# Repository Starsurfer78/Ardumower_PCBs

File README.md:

DIY Robot Lawn Mower Community: https://www.diy-robot-lawn-mower.com/

# Simple Ardumower_PCBs

If you want to buy a Board, you can send me an E-Mail: info@projekt-heimwerken.de

# Simple MainPCB only for Arduino DUE or Grand Central

New Board Design. All Pins from Software are now on the PCB. 
Supports 4 Motor Driver for Mowing.
Only a few Electronic Parts are needed. 
- JST-XH Connectors
- Screw Terminal 5.04mm
- Resistors
- Pin Header Connector 2.54mm
- Active Buzzer
- LED
- Jumper

Tested with MC33926 motor driver. Brushless Motordriver did not work at the Moment with Azuritber.

# Power PCB for Simple MainPCB

The charging board and the power supply for the motors are on a separate board.

Should also fit into small housings.

Use it at your own Risk.

Projekt: https://forum.ardumower.de/

Software Azuritber: https://github.com/Boilevin/AzuritBer

Ardumower Original Software: https://github.com/Ardumower

Facebook Gruppe DIY Robot Lawn Mower: https://www.facebook.com/groups/319588508137220

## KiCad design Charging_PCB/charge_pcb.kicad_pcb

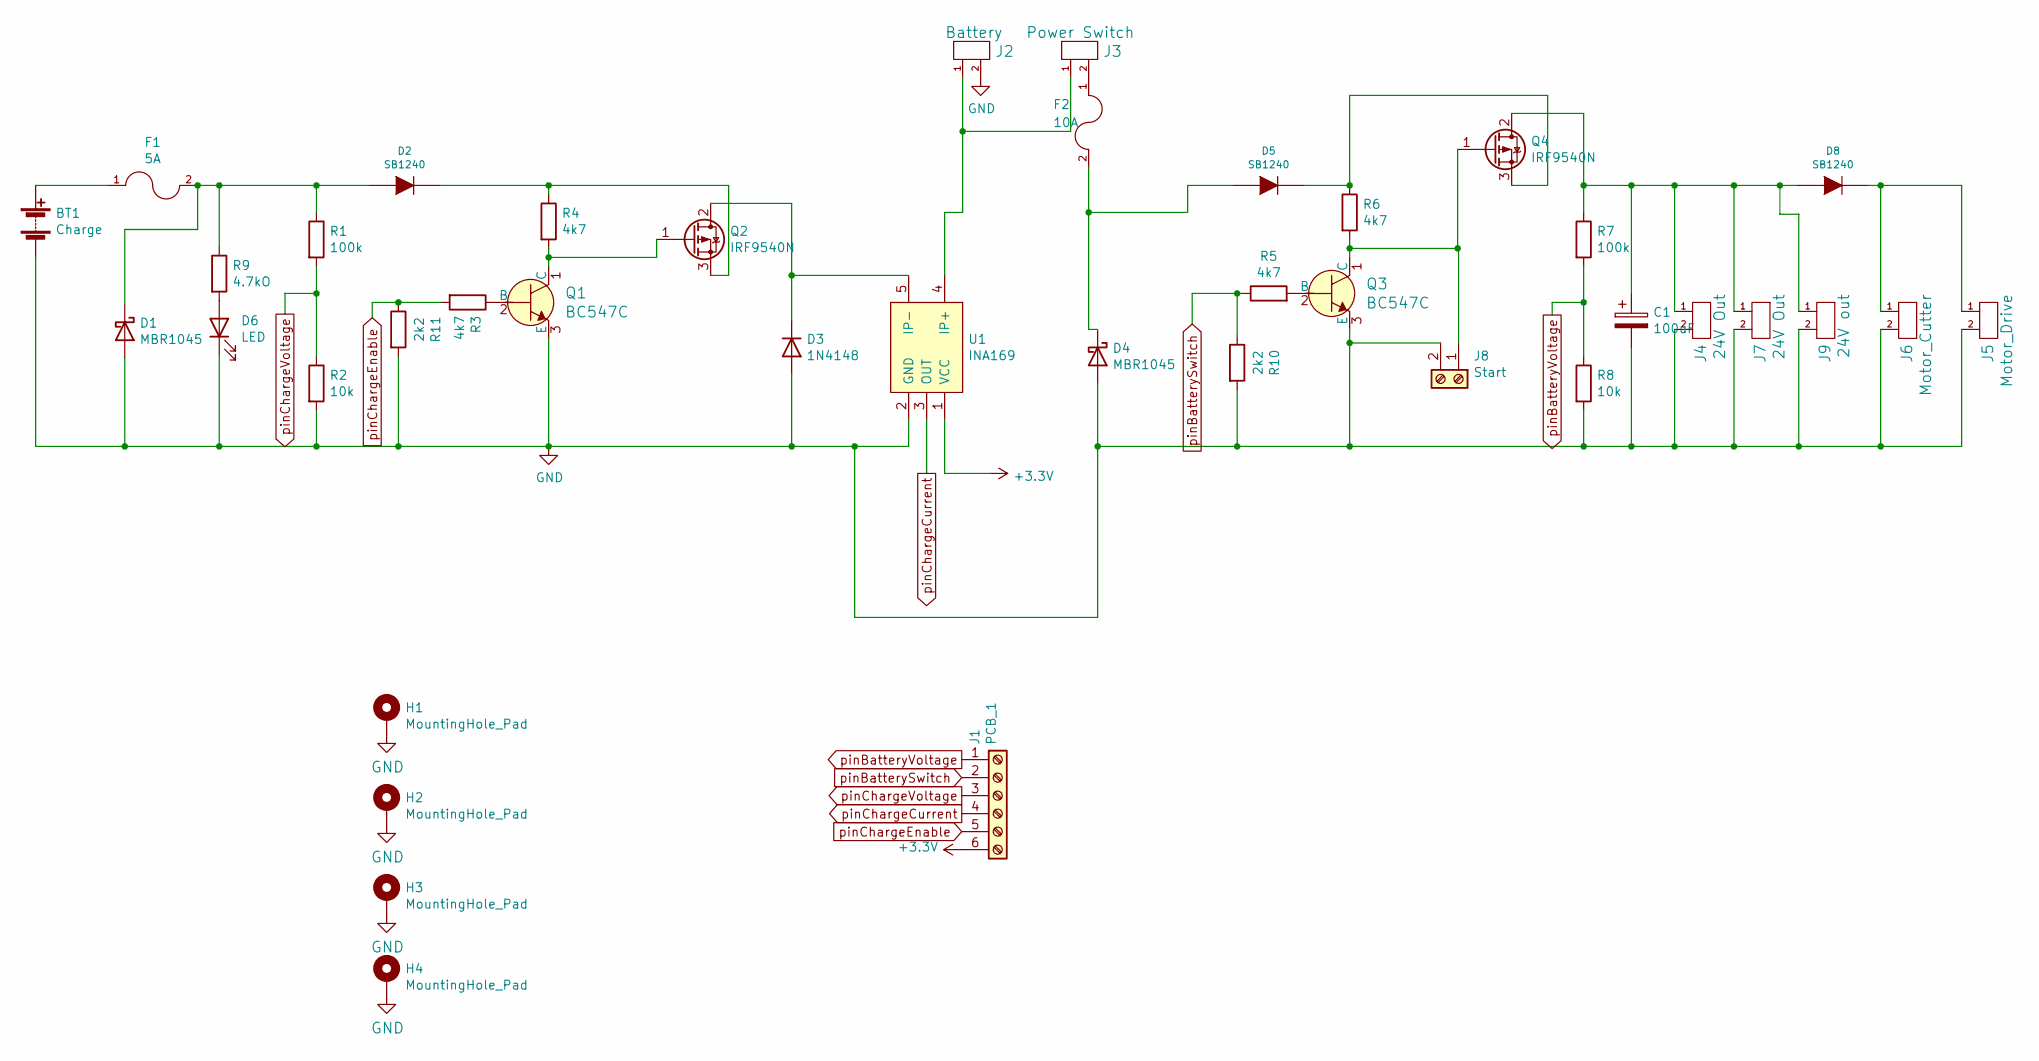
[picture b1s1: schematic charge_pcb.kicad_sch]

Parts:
BT1: Charge; Anschlussklemme_2P_RM5,08
C1: 100uF; Elko_vert_11.2x6.3mm_RM2.5
D1, D4: MBR1045; TO-220-2_Vertical
D2, D5, D8: SB1240; D_DO-41_SOD81_P10.16mm_Horizontal
D3: 1N4148; D_DO-35_SOD27_P7.62mm_Horizontal
D6: LED; LED_D1.8mm_W3.3mm_H2.4mm
F1: 5A; Fuseholder_Reichelt_PL112000
F2: 10A; Fuseholder_Reichelt_PL112000
H1, H2, H3, H4: MountingHole_Pad; MountingHole_3.2mm_M3_DIN965_Pad_TopBottom
J1: PCB_1; JST_XH_B6B-XH-A_1x06_P2.50mm_Vertical
J2: Battery; TerminalBlock_bornier-2_P5.08mm
J3: Power Switch; TerminalBlock_bornier-2_P5.08mm
J4, J7: 24V Out; TerminalBlock_bornier-2_P5.08mm
J5: Motor_Drive; TerminalBlock_bornier-2_P5.08mm
J6: Motor_Cutter; TerminalBlock_bornier-2_P5.08mm
J8: Start; JST_XH_B2B-XH-A_1x02_P2.50mm_Vertical
J9: 24V out; TerminalBlock_bornier-2_P5.08mm
Q1, Q3: BC547C; TO-92-3_Formed_Leads; MPN BC548BTA; Digi-Key_PN BC548BTACT-ND
Q2, Q4: IRF9540N; TO-220-3_Vertical
R1, R7: 100k; R_Axial_DIN0207_L6.3mm_D2.5mm_P7.62mm_Horizontal
R2, R8: 10k; R_Axial_DIN0207_L6.3mm_D2.5mm_P7.62mm_Horizontal
R3, R4, R5, R6: 4k7; R_Axial_DIN0207_L6.3mm_D2.5mm_P7.62mm_Horizontal
R9: 4.7kO; R_Axial_DIN0207_L6.3mm_D2.5mm_P7.62mm_Horizontal
R10, R11: 2k2; R_Axial_DIN0207_L6.3mm_D2.5mm_P7.62mm_Horizontal
U1: INA169; INA169_mit_Pinnummern

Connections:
+3V3: J1.6, U1.1 (VCC)
GND: BT1.2 (-), C1.2, D1.2 (A), D3.2 (A), D4.2 (A), D6.1 (K), H1.1, H2.1, H3.1, H4.1, J2.2, J4.2, J5.2, J6.2, J7.2, J8.2, J9.2, Q1.3 (E), Q3.3 (E), R2.2, R8.2, R10.2, R11.2, U1.2 (GND)
unnamed: BT1.1 (+), F1.1
unnamed: C1.1, D8.1 (A), J4.1, J7.1, J9.1, Q4.2 (D), R7.1
unnamed: D1.1 (K), D2.1 (A), F1.2, R1.1, R9.1
unnamed: D2.2 (K), Q2.3 (S), R4.1
unnamed: D3.1 (K), Q2.2 (D), U1.5 (IP-)
unnamed: D4.1 (K), D5.1 (A), F2.2
unnamed: D5.2 (K), Q4.3 (S), R6.1
unnamed: D6.2 (A), R9.2
unnamed: D8.2 (K), J5.1, J6.1
unnamed: F2.1, J3.2
unnamed: J2.1, J3.1, U1.4 (IP+)
unnamed: J8.1, Q3.1 (C), Q4.1 (G), R6.2
unnamed: Q1.1 (C), Q2.1 (G), R4.2
unnamed: Q1.2 (B), R3.1
unnamed: Q3.2 (B), R5.2
pinBatterySwitch: J1.2, R5.1, R10.1
pinBatteryVoltage: J1.1, R7.2, R8.1
pinChargeCurrent: J1.4, U1.3 (OUT)
pinChargeEnable: J1.5, R3.2, R11.1
pinChargeVoltage: J1.3, R1.2, R2.1

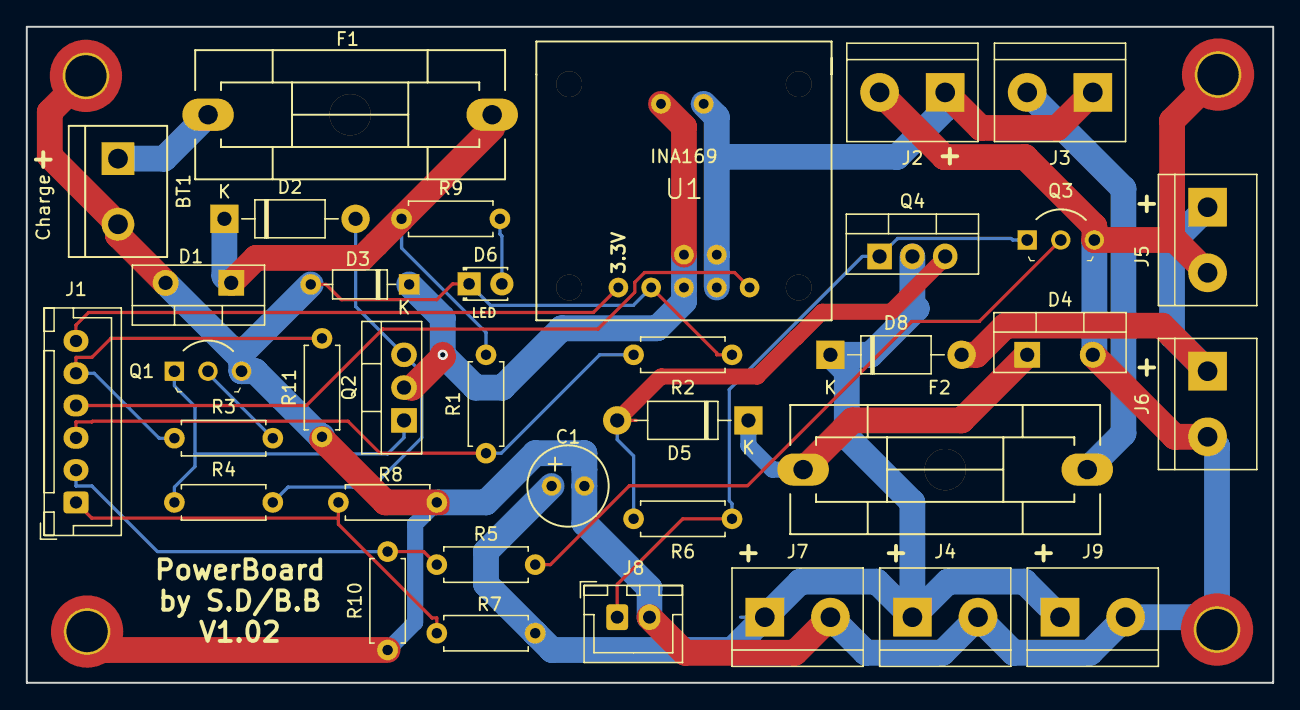
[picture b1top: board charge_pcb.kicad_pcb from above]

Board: 2 copper layers, 96.5 x 50.8 mm, 40 parts (0 on the bottom side), 22 nets.

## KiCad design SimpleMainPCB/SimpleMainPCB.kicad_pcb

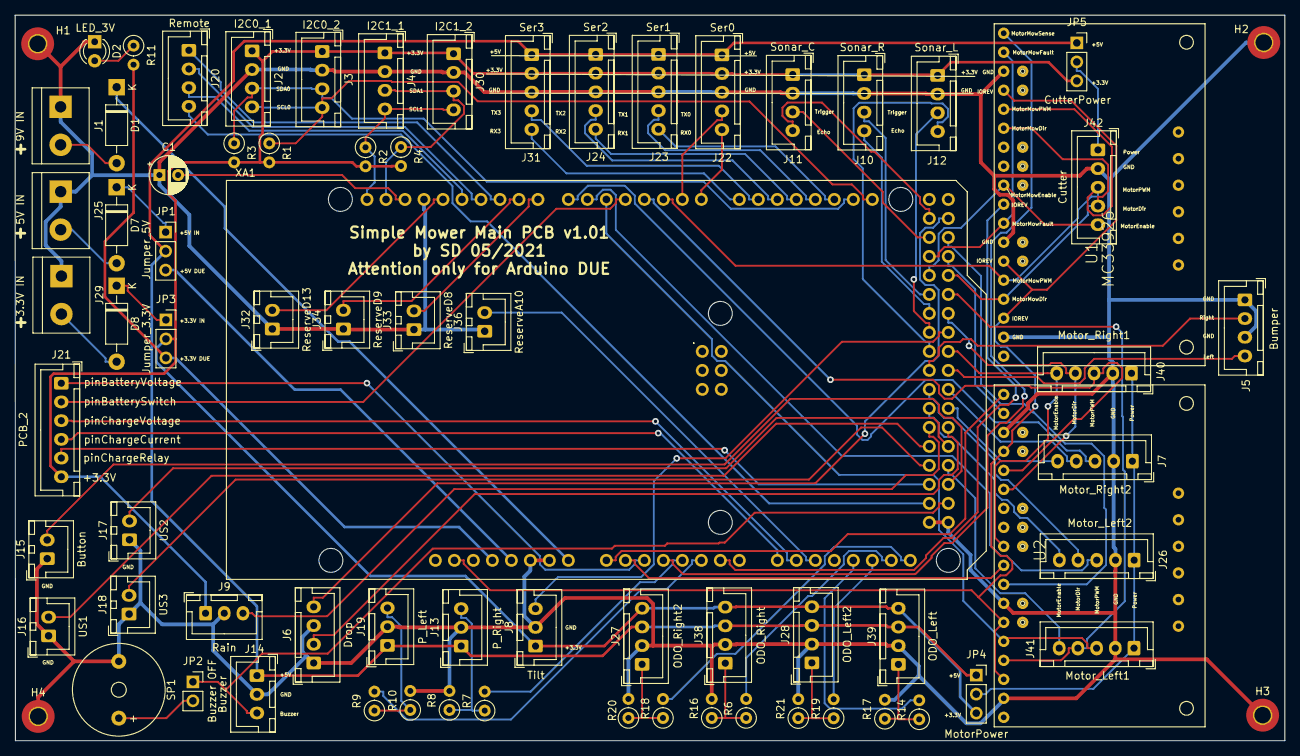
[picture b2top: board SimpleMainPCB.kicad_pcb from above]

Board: 2 copper layers, 169.8 x 97.0 mm, 75 parts (0 on the bottom side), 93 nets.

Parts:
C1: 100nF; CP_Radial_D5.0mm_P2.50mm
D1, D7, D8: 1N5819; D_DO-41_SOD81_P10.16mm_Horizontal
D2: LED_3V; LED_D3.0mm
H1, H2, H3, H4: MountingHole_Pad; MountingHole_2.2mm_M2_Pad_TopBottom
J1: 9V IN; TerminalBlock_bornier-2_P5.08mm
J2: I2C0_1; JST_XH_B4B-XH-A_1x04_P2.50mm_Vertical
J3: I2C0_2; JST_XH_B4B-XH-A_1x04_P2.50mm_Vertical
J4: I2C1_1; JST_XH_B4B-XH-A_1x04_P2.50mm_Vertical
J5: Bumper; JST_XH_B4B-XH-A_1x04_P2.50mm_Vertical
J6: Drop; JST_XH_B4B-XH-A_1x04_P2.50mm_Vertical
J7: Motor_Right2; JST_XH_B5B-XH-A_1x05_P2.50mm_Vertical
J8: Tilt; JST_XH_B3B-XH-A_1x03_P2.50mm_Vertical
J9: Rain; JST_XH_B3B-XH-A_1x03_P2.50mm_Vertical
J10: Sonar_R; JST_XH_B4B-XH-A_1x04_P2.50mm_Vertical
J11: Sonar_C; JST_XH_B4B-XH-A_1x04_P2.50mm_Vertical
J12: Sonar_L; JST_XH_B4B-XH-A_1x04_P2.50mm_Vertical
J13: P_Right; JST_XH_B3B-XH-A_1x03_P2.50mm_Vertical
J14: Buzzer; JST_XH_B3B-XH-A_1x03_P2.50mm_Vertical
J15: Button; JST_XH_B2B-XH-A_1x02_P2.50mm_Vertical
J16: US1; JST_XH_B2B-XH-A_1x02_P2.50mm_Vertical
J17: US2; JST_XH_B2B-XH-A_1x02_P2.50mm_Vertical
J18: US3; JST_XH_B2B-XH-A_1x02_P2.50mm_Vertical
J19: P_Left; JST_XH_B3B-XH-A_1x03_P2.50mm_Vertical
J20: Remote; JST_XH_B4B-XH-A_1x04_P2.50mm_Vertical
J21: PCB_2; JST_XH_B6B-XH-A_1x06_P2.50mm_Vertical
J22: Ser0; JST_XH_B5B-XH-A_1x05_P2.50mm_Vertical
J23: Ser1; JST_XH_B5B-XH-A_1x05_P2.50mm_Vertical
J24: Ser2; JST_XH_B5B-XH-A_1x05_P2.50mm_Vertical
J25: 5V IN; TerminalBlock_bornier-2_P5.08mm
J26: Motor_Left2; JST_XH_B5B-XH-A_1x05_P2.50mm_Vertical
J27: ODO_Right2; JST_XH_B4B-XH-A_1x04_P2.50mm_Vertical
J28: ODO_Left2; JST_XH_B4B-XH-A_1x04_P2.50mm_Vertical
J29: 3.3V IN; TerminalBlock_bornier-2_P5.08mm
J30: I2C1_2; JST_XH_B4B-XH-A_1x04_P2.50mm_Vertical
J31: Ser3; JST_XH_B5B-XH-A_1x05_P2.50mm_Vertical
J32: ReserveD13; JST_XH_B2B-XH-A_1x02_P2.50mm_Vertical
J33: ReserveD8; JST_XH_B2B-XH-A_1x02_P2.50mm_Vertical
J34: ReserveD9; JST_XH_B2B-XH-A_1x02_P2.50mm_Vertical
J36: ReserveA10; JST_XH_B2B-XH-A_1x02_P2.50mm_Vertical
J38: ODO_Right; JST_XH_B4B-XH-A_1x04_P2.50mm_Vertical
J39: ODO_Left; JST_XH_B4B-XH-A_1x04_P2.50mm_Vertical
J40: Motor_Right1; JST_XH_B5B-XH-A_1x05_P2.50mm_Vertical
J41: Motor_Left1; JST_XH_B5B-XH-A_1x05_P2.50mm_Vertical
J42: Cutter; JST_XH_B5B-XH-A_1x05_P2.50mm_Vertical
JP1: Jumper_5V; PinSocket_1x03_P2.54mm_Vertical
JP2: Buzzer OFF; PinSocket_1x02_P2.54mm_Vertical
JP3: Jumper_3.3V; PinSocket_1x03_P2.54mm_Vertical
JP4: MotorPower; PinSocket_1x03_P2.54mm_Vertical
JP5: CutterPower; PinSocket_1x03_P2.54mm_Vertical
R1, R2, R3, R4: XXX; R_Axial_DIN0207_L6.3mm_D2.5mm_P2.54mm_Vertical
R6, R7, R9, R14, R18, R19: 1KO; R_Axial_DIN0207_L6.3mm_D2.5mm_P2.54mm_Vertical
R8, R10: 1.5KO; R_Axial_DIN0207_L6.3mm_D2.5mm_P2.54mm_Vertical
R11: 100; R_Axial_DIN0207_L6.3mm_D2.5mm_P2.54mm_Vertical
R16, R17, R20, R21: 1,5KO; R_Axial_DIN0207_L6.3mm_D2.5mm_P2.54mm_Vertical
SP1: SPEAKER; Buzzer_12x9.5RM7.6
U1, U2: MC33926; MC_33926_31polig_mit_Bohrloch_neue_Masse
XA1: Arduino_Due_Shield

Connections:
+3V3: J2.1, J3.1, J4.1, J8.1, J9.1, J10.1, J11.1, J12.1, J21.6, J22.2, J23.2, J24.2, J27.4, J28.4, J30.1, J31.2, J38.4, J39.4, JP3.2, JP4.3, JP5.3, R1.2, R2.2, R3.2, R4.2
+5V: J13.1, J14.1, J19.1, J22.1, J23.1, J24.1, J27.3, J28.3, J31.1, J38.3, J39.3, JP1.2, JP4.1, JP5.1
+9V: D1.1, XA1.VIN
DUE_3.3V: JP3.3, R11.2, XA1.3V3
DUE_5V: JP1.3, XA1.5V1
GND: C1.1, D2.1, H1.1, H2.1, H3.1, H4.1, J1.1, J2.2, J3.2, J4.2, J5.1, J5.3, J6.1, J6.3, J7.2, J8.2, J9.2, J10.2, J11.2, J12.2, J13.2, J14.2, J15.1, J16.1, J17.1, J18.1, J19.2, J22.3, J23.3, J24.3, J25.1, J26.2, J27.2, J28.2, J29.1, J30.2, J31.3, J32.1, J33.1, J34.1, J36.1, J38.2, J39.2, J40.2, J41.2, J42.2, R8.2, R10.2, R16.2, R17.2, R20.2, R21.2, SP1.1, U1.2, U1.7, U1.16, U2.2, U2.7, U2.16, XA1.GND1, XA1.GND2, XA1.GND3, XA1.GND5, XA1.GND6
IOREV: U1.3, U1.6, U1.15, U2.3, U2.6, U2.15, XA1.IORF
unnamed: C1.2, XA1.AREF
unnamed: D1.2, J1.2
unnamed: D2.2, R11.1
unnamed: D7.1, JP1.1
unnamed: D7.2, J25.2
unnamed: D8.1, JP3.1
unnamed: D8.2, J29.2
unnamed: J13.3, R7.1, R8.1
unnamed: J19.3, R9.1, R10.1
unnamed: J7.1, J26.1, J40.1, J41.1, JP4.2
unnamed: J27.1, R18.1, R20.1
unnamed: J28.1, R19.1, R21.1
unnamed: J38.1, R6.1, R16.1
unnamed: J39.1, R14.1, R17.1
unnamed: J42.1, JP5.2
unnamed: JP2.2, SP1.2
RX0: J22.5, XA1.D0
RX1: J23.5, XA1.D19
RX2: J24.5, XA1.D17
RX3: J31.5, XA1.D14
SCL0: J2.4, J3.4, R1.1, XA1.D21
SCL1: J4.4, J30.4, R2.1, XA1.SCL1
SDA0: J2.3, J3.3, R3.1, XA1.D20
SDA1: J4.3, J30.3, R4.1, XA1.SDA1
TX0: J22.4, XA1.D1
TX1: J23.4, XA1.D18
TX2: J24.4, XA1.D16
TX3: J31.4, XA1.D15
pinBatterySwitch: J21.2, XA1.D4
pinBatteryVoltage: J21.1, XA1.A2
pinBumperLeft: J5.4, XA1.D39
pinBumperRight: J5.2, XA1.D38
pinButton: J15.2, XA1.D51
pinBuzzer: J14.3, JP2.1, XA1.D53
pinChargeCurrent: J21.4, XA1.A8
pinChargeEnable: J21.5, XA1.D50
pinChargeVoltage: J21.3, XA1.A9
pinDropLeft: J6.2, XA1.D45
pinDropRight: J6.4, XA1.D23
pinMotorEnable: J40.5, U2.10, XA1.D37
pinMotorLeft2Dir: J26.4, XA1.D40
pinMotorLeft2Enable: J26.5, XA1.D42
pinMotorLeft2PWM: J26.3, XA1.D6
pinMotorLeftDir: J41.4, U2.4, XA1.D31
pinMotorLeftEnable: J41.5, XA1.D49
pinMotorLeftFault: U2.8, XA1.D25
pinMotorLeftPWM: J41.3, U2.5, XA1.D5
pinMotorLeftSense: U2.9, XA1.A1
pinMotorMow1Sense: U1.9, XA1.A6
pinMotorMowDir: J42.4, U1.4, U1.13, XA1.D29
pinMotorMowEnable: J42.5, U1.10, XA1.D28
pinMotorMowFault: U1.8, U1.17, XA1.D26
pinMotorMowPWM: J42.3, U1.5, U1.14, XA1.D2
pinMotorMowSense: U1.18, XA1.A3
pinMotorRight2Dir: J7.4, XA1.D41
pinMotorRight2Enable: J7.5, XA1.D43
pinMotorRight2PWM: J7.3, XA1.D7
pinMotorRightDir: J40.4, U2.13, XA1.D33
pinMotorRightFault: U2.17, XA1.D27
pinMotorRightPWM: J40.3, U2.14, XA1.D3
pinMotorRightSense: U2.18, XA1.A0
pinOdometryLeft: R14.2, XA1.DAC0
pinOdometryLeft2: R19.2, XA1.DAC1
pinOdometryRight: R6.2, XA1.CANR
pinOdometryRight2: R18.2, XA1.CANT
pinPerimeterLeft: R9.2, XA1.A5
pinPerimeterRight: R7.2, XA1.A4
pinRain: J9.3, XA1.D44
pinRemoteMow: J20.3, XA1.D12
pinRemoteSpeed: J20.1, XA1.D10
pinRemoteSteer: J20.2, XA1.D11
pinRemoteSwitch: J20.4, XA1.D52
pinReserveA10: J36.2, XA1.A10
pinReserveD8: J33.2, XA1.D8
pinReserveD9: J34.2, XA1.D9
pinReserveD13: J32.2, XA1.D13
pinSonarCenterEcho: J11.4, XA1.D22
pinSonarCenterTrigger: J11.3, XA1.D24
pinSonarLeftEcho: J12.4, XA1.D36
pinSonarLeftTrigger: J12.3, XA1.D34
pinSonarRightEcho: J10.4, XA1.D32
pinSonarRightTrigger: J10.3, XA1.D30
pinTilt: J8.3, XA1.D35
pinUserSwitch1: J16.2, XA1.D46
pinUserSwitch2: J17.2, XA1.D47
pinUserSwitch3: J18.2, XA1.D48

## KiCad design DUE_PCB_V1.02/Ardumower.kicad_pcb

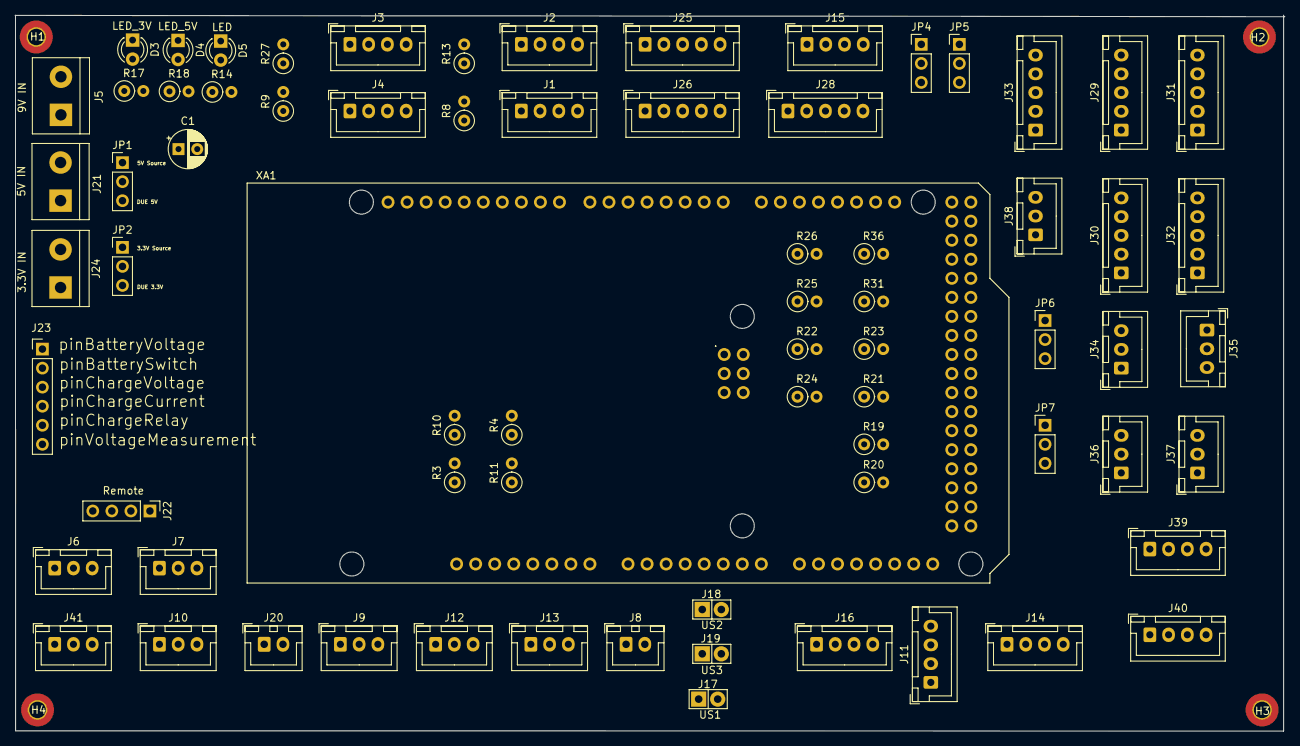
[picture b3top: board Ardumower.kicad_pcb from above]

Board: 2 copper layers, 169.3 x 95.5 mm, 76 parts (0 on the bottom side), 87 nets, no tracks yet.

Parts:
C1: 100nF; CP_Radial_D5.0mm_P2.50mm
D3: LED_3V; LED_D3.0mm
D4: LED_5V; LED_D3.0mm
D5: LED; LED_D3.0mm
H1, H2, H3, H4: MountingHole_Pad; MountingHole_2.2mm_M2_Pad_TopBottom
J1: I2C0_1; JST_XH_B4B-XH-A_1x04_P2.50mm_Vertical
J2: I2C0_2; JST_XH_B4B-XH-A_1x04_P2.50mm_Vertical
J3: I2C1_1; JST_XH_B4B-XH-A_1x04_P2.50mm_Vertical
J4: I2C1_2; JST_XH_B4B-XH-A_1x04_P2.50mm_Vertical
J5: 9V IN; TerminalBlock_bornier-2_P5.08mm
J6: Drop_Left; JST_XH_B3B-XH-A_1x03_P2.50mm_Vertical
J7: Drop_Right; JST_XH_B3B-XH-A_1x03_P2.50mm_Vertical
J8: Tilt; JST_XH_B2B-XH-A_1x02_P2.50mm_Vertical
J9: Rain; JST_XH_B3B-XH-A_1x03_P2.50mm_Vertical
J10: Bumper; JST_XH_B3B-XH-A_1x03_P2.50mm_Vertical
J11: Sonar_C; JST_XH_B4B-XH-A_1x04_P2.50mm_Vertical
J12: P_Left; JST_XH_B3B-XH-A_1x03_P2.50mm_Vertical
J13: P_Right; JST_XH_B3B-XH-A_1x03_P2.50mm_Vertical
J14: Sonar_R; JST_XH_B4B-XH-A_1x04_P2.50mm_Vertical
J15: Ser2 ESP32; JST_XH_B4B-XH-A_1x04_P2.50mm_Vertical
J16: Sonar_L; JST_XH_B4B-XH-A_1x04_P2.50mm_Vertical
J17: US1; Pin_Header_KK110_1x02_3D
J18: US2; Pin_Header_KK110_1x02_3D
J19: US3; Pin_Header_KK110_1x02_3D
J20: Button; JST_XH_B2B-XH-A_1x02_P2.50mm_Vertical
J21: 5V IN; TerminalBlock_bornier-2_P5.08mm
J22: Remote; PinHeader_1x04_P2.54mm_Vertical
J23: PCB_2; PinHeader_1x06_P2.54mm_Vertical
J24: 3.3V IN; TerminalBlock_bornier-2_P5.08mm
J25: Ser0; JST_XH_B5B-XH-A_1x05_P2.50mm_Vertical
J26: Ser1; JST_XH_B5B-XH-A_1x05_P2.50mm_Vertical
J28: Ser3; JST_XH_B5B-XH-A_1x05_P2.50mm_Vertical
J29: Motor_Right1; JST_XH_B5B-XH-A_1x05_P2.50mm_Vertical
J30: Motor_Right2; JST_XH_B5B-XH-A_1x05_P2.50mm_Vertical
J31: Motor_Left1; JST_XH_B5B-XH-A_1x05_P2.50mm_Vertical
J32: Motor_Left2; JST_XH_B5B-XH-A_1x05_P2.50mm_Vertical
J33: Cutter_Motor; JST_XH_B5B-XH-A_1x05_P2.50mm_Vertical
J34: ODORight1; JST_XH_B3B-XH-A_1x03_P2.50mm_Vertical
J35: ODORight2; JST_XH_B3B-XH-A_1x03_P2.50mm_Vertical
J36: ODOLeft1; JST_XH_B3B-XH-A_1x03_P2.50mm_Vertical
J37: ODOLeft2; JST_XH_B3B-XH-A_1x03_P2.50mm_Vertical
J38: ODOCutter; JST_XH_B3B-XH-A_1x03_P2.50mm_Vertical
J39: MC33926 compatibility sense; JST_XH_B4B-XH-A_1x04_P2.50mm_Vertical
J40: MC33926 compatibility fault; JST_XH_B4B-XH-A_1x04_P2.50mm_Vertical
J41: Buzzer; JST_XH_B3B-XH-A_1x03_P2.50mm_Vertical
JP1: Jumper_5V; PinHeader_1x03_P2.54mm_Vertical
JP2: Jumper_3.3V; PinHeader_1x03_P2.54mm_Vertical
JP4: Motor_Driver_Power; PinHeader_1x03_P2.54mm_Vertical
JP5: Cutter_Power; PinHeader_1x03_P2.54mm_Vertical
JP6: ODO_Power; PinHeader_1x03_P2.54mm_Vertical
JP7: CRPM_Power; PinHeader_1x03_P2.54mm_Vertical
R3, R4, R19, R20, R21, R22, R31: 1KO; R_Axial_DIN0207_L6.3mm_D2.5mm_P2.54mm_Vertical
R8, R9, R13, R27: XXX; R_Axial_DIN0207_L6.3mm_D2.5mm_P2.54mm_Vertical
R10, R11, R23, R24, R25, R26, R36: 1.5KO; R_Axial_DIN0207_L6.3mm_D2.5mm_P2.54mm_Vertical
R14, R17: 100; R_Axial_DIN0207_L6.3mm_D2.5mm_P2.54mm_Vertical
R18: 220; R_Axial_DIN0207_L6.3mm_D2.5mm_P2.54mm_Vertical
XA1: Arduino_Due_Shield

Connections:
+3V3: J1.1, J2.1, J3.1, J4.1, J6.1, J7.1, J9.1, J11.1, J14.1, J16.1, J26.1, J28.1, JP2.2, JP4.1, JP5.1, JP6.1, JP7.1, R8.2, R9.2, R13.2, R17.2, R27.2
+5V: J12.1, J13.1, J26.5, J28.5, J41.1, JP1.2, JP4.3, JP5.3, JP6.3, JP7.3, R18.2
+9V: J5.2, J15.4, XA1.VIN
DUE_3.3V: JP2.3, XA1.3V3
DUE_5V: JP1.3, XA1.5V1
GND: C1.1, D3.1, D4.1, D5.1, H1.1, H2.1, H3.1, H4.1, J1.2, J2.2, J3.2, J4.2, J5.1, J6.2, J7.2, J8.1, J9.2, J10.1, J11.2, J12.2, J13.2, J14.2, J15.1, J16.2, J17.1, J18.1, J19.1, J20.1, J21.1, J24.1, J26.2, J28.2, J29.5, J30.5, J31.5, J32.5, J33.5, J34.3, J35.3, J36.3, J37.3, J38.3, J41.2, R10.2, R11.2, R23.2, R24.2, R25.2, R26.2, R36.2, XA1.GND1, XA1.GND2, XA1.GND3, XA1.GND5, XA1.GND6
unnamed: C1.2, XA1.AREF
unnamed: D3.2, R17.1
unnamed: D4.2, R18.1
unnamed: D5.2, R14.2
unnamed: J12.3, R3.1, R10.1
unnamed: J13.3, R4.1, R11.1
unnamed: J21.2, JP1.1
unnamed: J24.2, JP2.1
unnamed: J29.4, J30.4, J31.4, J32.4, JP4.2
unnamed: J33.4, JP5.2
unnamed: J34.1, R31.2, R36.1
unnamed: J34.2, J35.2, J36.2, J37.2, JP6.2
unnamed: J35.1, R19.2, R23.1
unnamed: J36.1, R20.2, R24.1
unnamed: J37.1, R21.2, R25.1
unnamed: J38.1, R22.2, R26.1
unnamed: J38.2, JP7.2
RX1: J26.3, XA1.D19
RX2: J15.2, XA1.D17
RX3: J28.3, XA1.D15
SCL0: J1.4, J2.4, R8.1, XA1.D21
SCL1: J3.4, J4.4, R9.1, XA1.SCL1
SDA0: J1.3, J2.3, R13.1, XA1.D20
SDA1: J3.3, J4.3, R27.1, XA1.SDA1
TX1: J26.4, XA1.D18
TX2: J15.3, XA1.D16
TX3: J28.4, XA1.D14
pinBatterySwitch: J23.2, XA1.D4
pinBatteryVoltage: J23.1, XA1.A2
pinBumperLeft: J10.3, XA1.D39
pinBumperRight: J10.2, XA1.D38
pinButton: J20.2, XA1.D51
pinBuzzer: J41.3, XA1.D53
pinChargeCurrent: J23.4, XA1.A8
pinChargeRelay: J23.5, XA1.D50
pinChargeVoltage: J23.3, XA1.A9
pinDropLeft: J6.3, XA1.D45
pinDropRight: J7.3, XA1.D23
pinLED: R14.1, XA1.D13
pinMotorEnable: J29.3, J30.3, J31.3, J32.3, XA1.D37
pinMotorLeft2Dir: J32.2, XA1.D40
pinMotorLeft2PWM: J32.1, XA1.D6
pinMotorLeftDir: J31.2, XA1.D31
pinMotorLeftFault: J40.2, XA1.D25
pinMotorLeftPWM: J31.1, XA1.D5
pinMotorLeftSense: J39.2, XA1.A1
pinMotorMow1Sense: J39.3, XA1.A6
pinMotorMow2Sense: J39.4, XA1.A3
pinMotorMowDir: J33.2, XA1.D29
pinMotorMowEnable: J33.3, XA1.D28
pinMotorMowFault: J40.3, XA1.D26
pinMotorMowPWM: J33.1, XA1.D2
pinMotorMowRpm: R22.1, XA1.A11
pinMotorRight2Dir: J30.2, XA1.D41
pinMotorRight2PWM: J30.1, XA1.D7
pinMotorRightDir: J29.2, XA1.D33
pinMotorRightFault: J40.1, XA1.D27
pinMotorRightPWM: J29.1, XA1.D3
pinMotorRightSense: J39.1, XA1.A0
pinOdometryLeft: R20.1, XA1.DAC0
pinOdometryLeft2: R21.1, XA1.DAC1
pinOdometryRight: R31.1, XA1.CANR
pinOdometryRight2: R19.1, XA1.CANT
pinPerimeterLeft: R3.2, XA1.A5
pinPerimeterRight: R4.2, XA1.A4
pinRain: J9.3, XA1.D44
pinRemoteMow: J22.3, XA1.D12
pinRemoteSpeed: J22.1, XA1.D10
pinRemoteSteer: J22.2, XA1.D11
pinRemoteSwitch: J22.4, XA1.D52
pinSonarCenterEcho: J11.3, XA1.D22
pinSonarCenterTrigger: J11.4, XA1.D24
pinSonarLeftEcho: J16.3, XA1.D36
pinSonarLeftTrigger: J16.4, XA1.D34
pinSonarRightEcho: J14.3, XA1.D32
pinSonarRightTrigger: J14.4, XA1.D30
pinTilt: J8.2, XA1.D35
pinUserSwitch1: J17.2, XA1.D46
pinUserSwitch2: J18.2, XA1.D47
pinUserSwitch3: J19.2, XA1.D48
pinVoltageMeasurement: J23.6, XA1.A7

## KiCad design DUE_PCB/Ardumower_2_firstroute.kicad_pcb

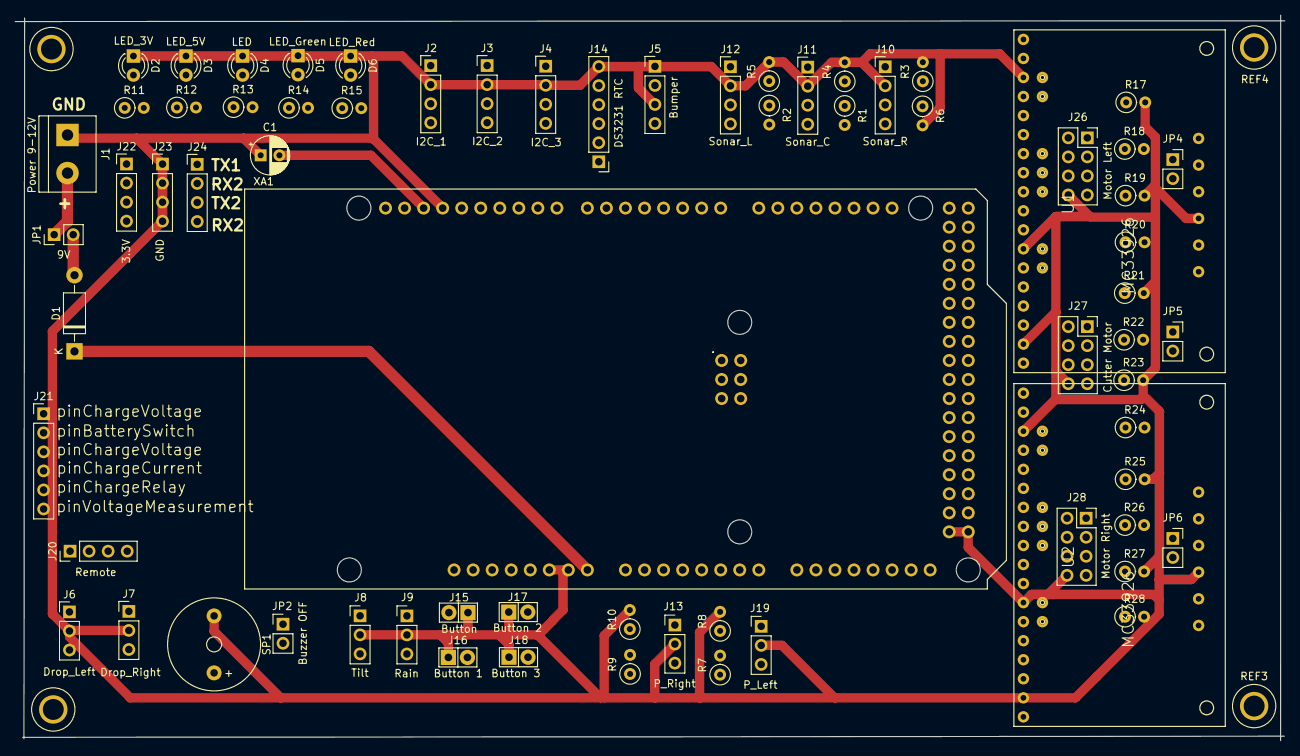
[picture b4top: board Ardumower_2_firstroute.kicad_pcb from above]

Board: 2 copper layers, 169.3 x 96.8 mm, 73 parts (0 on the bottom side), 87 nets.

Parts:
C1: 100nF; CP_Radial_D5.0mm_P2.50mm
D1: 1N5819; D_DO-41_SOD81_P10.16mm_Horizontal
D2: LED_3V; LED_D3.0mm
D3: LED_5V; LED_D3.0mm
D4: LED; LED_D3.0mm
D5: LED_Green; LED_D3.0mm
D6: LED_Red; LED_D3.0mm
J1: Power 9-12V; TerminalBlock_bornier-2_P5.08mm
J2: I2C_1; PinHeader_1x04_P2.54mm_Vertical
J3: I2C_2; PinHeader_1x04_P2.54mm_Vertical
J4: I2C_3; PinHeader_1x04_P2.54mm_Vertical
J5: Bumper; PinHeader_1x04_P2.54mm_Vertical
J6: Drop_Left; PinHeader_1x03_P2.54mm_Vertical
J7: Drop_Right; PinHeader_1x03_P2.54mm_Vertical
J8: Tilt; PinHeader_1x03_P2.54mm_Vertical
J9: Rain; PinHeader_1x03_P2.54mm_Vertical
J10: Sonar_R; PinHeader_1x04_P2.54mm_Vertical
J11: Sonar_C; PinHeader_1x04_P2.54mm_Vertical
J12: Sonar_L; PinHeader_1x04_P2.54mm_Vertical
J13: P_Right; PinHeader_1x03_P2.54mm_Vertical
J14: DS3231 RTC; PinHeader_1x06_P2.54mm_Vertical
J15: Button; Pin_Header_KK110_1x02_3D
J16: Button 1; Pin_Header_KK110_1x02_3D
J17: Button 2; Pin_Header_KK110_1x02_3D
J18: Button 3; Pin_Header_KK110_1x02_3D
J19: P_Left; PinHeader_1x03_P2.54mm_Vertical
J20: Remote; PinHeader_1x04_P2.54mm_Vertical
J21: PCB_2; PinHeader_1x06_P2.54mm_Vertical
J22: 3.3V; PinHeader_1x04_P2.54mm_Vertical
J23: GND; PinHeader_1x04_P2.54mm_Vertical
J24: RX & TX; PinHeader_1x04_P2.54mm_Vertical
J26: Motor Left; PinSocket_2x04_P2.54mm_Vertical
J27: Cutter Motor; PinSocket_2x04_P2.54mm_Vertical
J28: Motor Right; PinSocket_2x04_P2.54mm_Vertical
JP1: 9V; PinHeader_1x02_P2.54mm_Vertical
JP2: Buzzer OFF; PinHeader_1x02_P2.54mm_Vertical
JP4, JP5, JP6: 5V; PinSocket_1x02_P2.54mm_Vertical
R1, R2, R3, R7, R9, R18, R20, R22, R24, R26, R28: 1KO; R_Axial_DIN0207_L6.3mm_D2.5mm_P2.54mm_Vertical
R4, R5, R6: 2KO; R_Axial_DIN0207_L6.3mm_D2.5mm_P2.54mm_Vertical
R8, R10, R17, R19, R21, R23, R25, R27: 1.5KO; R_Axial_DIN0207_L6.3mm_D2.5mm_P2.54mm_Vertical
R11, R13, R14, R15: 100; R_Axial_DIN0207_L6.3mm_D2.5mm_P2.54mm_Vertical
R12: 220; R_Axial_DIN0207_L6.3mm_D2.5mm_P2.54mm_Vertical
REF2, REF3, REF4: Test-Point-Pin_Drill2.79mm
SP1: SPEAKER; Buzzer_12x9.5RM7.6
U1, U2: MC33926; MC_33926_31polig_mit_Bohrloch_neue_Masse
XA1: Arduino_Due_Shield

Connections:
+3V3: J2.1, J3.1, J4.1, J6.1, J7.1, J8.1, J9.1, J14.5, J22.1, J22.2, J22.3, J22.4, R11.2, XA1.3V3
+5V: J10.1, J11.1, J12.1, J13.1, J19.1, JP4.1, JP5.1, JP6.1, R12.2, XA1.5V1
+9V: D1.1, XA1.VIN
+24V: U1.22, U2.22
GND: C1.1, D2.1, D3.1, D4.1, D5.1, D6.1, J1.1, J2.2, J3.2, J4.2, J5.1, J5.3, J6.2, J7.2, J8.2, J9.2, J10.2, J11.2, J12.2, J13.2, J14.6, J15.1, J16.1, J17.1, J18.1, J19.2, J23.1, J23.2, J23.3, J23.4, J26.8, J27.8, J28.8, R4.2, R5.2, R6.2, R8.2, R10.2, R17.2, R19.2, R21.2, R23.2, R25.2, R27.2, SP1.1, U1.2, U1.7, U1.16, U1.21, U2.2, U2.7, U2.16, U2.21, XA1.GND1, XA1.GND2, XA1.GND3, XA1.GND5, XA1.GND6
IOREV: U1.3, U1.6, U1.9, U1.15, U2.3, U2.6, U2.15, XA1.IORF
MotorBreak: J26.3, J28.3
unnamed: C1.2, XA1.AREF
unnamed: D1.2, JP1.2
unnamed: D2.2, R11.1
unnamed: D3.2, R12.1
unnamed: D4.2, R13.2
unnamed: D5.2, R14.2
unnamed: D6.2, R15.2
unnamed: J1.2, JP1.1
unnamed: J10.3, R3.1, R6.1
unnamed: J11.3, R1.1, R4.1
unnamed: J12.3, R2.1, R5.1
unnamed: J13.3, R7.1, R8.1
unnamed: J19.3, R9.1, R10.1
unnamed: J26.1, JP4.2
unnamed: J26.6, R17.1, R18.1
unnamed: J26.7, R19.1, R20.1
unnamed: J27.1, JP5.2
unnamed: J27.6, R21.1, R22.1
unnamed: J27.7, R23.1, R24.1
unnamed: J28.1, JP6.2
unnamed: J28.6, R25.1, R26.1
unnamed: J28.7, R27.1, R28.1
unnamed: JP2.2, SP1.2
RX1: J24.2, XA1.D19
RX2: J24.4, XA1.D17
SCL0: J2.4, J3.4, XA1.D21
SCL1: J4.4, J14.3, XA1.SCL1
SDA0: J2.3, J3.3, XA1.D20
SDA1: J4.3, J14.4, XA1.SDA1
TX1: J24.1, XA1.D18
TX2: J24.3, XA1.D16
pinBatterySwitch: J21.2, XA1.D4
pinBatteryVoltage: J21.1, XA1.A2
pinBumperLeft: J5.4, XA1.D39
pinBumperRight: J5.2, XA1.D38
pinButton: J15.2, XA1.D51
pinBuzzer: JP2.1, XA1.D53
pinChargeCurrent: J21.4, XA1.A8
pinChargeRelay: J21.5, XA1.D50
pinChargeVoltage: J21.3, XA1.A9
pinDropLeft: J6.3, XA1.D45
pinDropRight: J7.3, XA1.D23
pinGreenLED: R14.1, XA1.D6
pinLED: R13.1, XA1.D13
pinMotorEnable: J26.5, J28.5, U2.10, XA1.D37
pinMotorLeftDir: J26.2, U2.4, XA1.D31
pinMotorLeftFault: R20.2, U2.8, XA1.D25
pinMotorLeftPWM: J26.4, U2.5, XA1.D5
pinMotorLeftSense: U2.9, XA1.A1
pinMotorMowDir: J27.2, U1.4, U1.13, XA1.D29
pinMotorMowEnable: J27.5, U1.10, XA1.D28
pinMotorMowFault: R24.2, U1.8, U1.17, XA1.D26
pinMotorMowPWM: J27.4, U1.5, U1.14, XA1.D2
pinMotorMowRpm: R22.2, XA1.A11
pinMotorMowSense: U1.18, XA1.A3
pinMotorRightDir: J28.2, U2.13, XA1.D33
pinMotorRightFault: R28.2, U2.17, XA1.D27
pinMotorRightPWM: J28.4, U2.14, XA1.D3
pinMotorRightSense: U2.18, XA1.A0
pinOdometryLeft: R18.2, XA1.DAC0
pinOdometryRight: R26.2, XA1.CANR
pinPerimeterLeft: R9.2, XA1.A5
pinPerimeterRight: R7.2, XA1.A4
pinRain: J9.3, XA1.D44
pinRedLED: R15.1, XA1.D7
pinRemoteMow: J20.3, XA1.D12
pinRemoteSpeed: J20.1, XA1.D10
pinRemoteSteer: J20.2, XA1.D11
pinRemoteSwitch: J20.4, XA1.D52
pinSonarCenterEcho: J11.4, XA1.D22
pinSonarCenterTrigger: R1.2, XA1.D24
pinSonarLeftEcho: J12.4, XA1.D36
pinSonarLeftTrigger: R2.2, XA1.D34
pinSonarRightEcho: J10.4, XA1.D32
pinSonarRightTrigger: R3.2, XA1.D30
pinTilt: J8.3, XA1.D35
pinUserSwitch1: J16.2, XA1.D46
pinUserSwitch2: J17.2, XA1.D47
pinUserSwitch3: J18.2, XA1.D48
pinVoltageMeasurement: J21.6, XA1.A7

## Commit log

2021-04-08 First Start
2021-04-08 Starsurfer78
    Sorting the Footprints on PCB
2021-04-08 Add Image Folder
    Add PCB 3D Image
2021-04-10 Charging Board
2021-04-11 Chargin Board changes
2021-04-11 Change Name of Mosfet
2021-04-11 Add Gerber Files
2021-04-11 File changes
2021-04-14 PCB Changes
2021-05-03 New Version startet
2021-05-03 Rename Directory
2021-05-04 Add Power Connector for 5V and 3.3V
2021-05-04 Design changes
2021-05-04 Add new PCB Image
2021-05-06 first test
    JP2 and JP3 redraw
2021-05-06 Ad new RX TX Connector and some other improvements
2021-05-06 test
2021-05-07 Change Connector Type
2021-05-07 Update Ardumower.sch-bak
2021-05-07 Change Jumper for Power Source
    Change Screw Terminal for 5V/3.3V to jumper.
2021-05-07 Change LED Power Source
    Change the Power Source from the LED_5V and LED_3.3V
2021-05-07 Change D6 and D7
    Add Description for PIN D6 and D7 to pinFrontMotorLeft and pinFrontMotorRight
2021-05-07 Rename Pins
    Rename pinFrontMotorLeft to pinMotorLeft2PWM and pinFrontMotorRight to pinMotorRight2PWM
2021-05-07 Add new Connectors for 4 Mow Motors and Odometrie
    Add new Connectors for 4 Mow Motors and Odometrie
2021-05-07 Add new Motor Schematic
    Add new Motor Schematic
2021-05-08 Remove Lawn Sense Pins
    Remove Lawn Sense Pins and add pinMotorLeft2Dir and pinMotorRight2Dir
2021-05-08 Remove Resistors
    Remove R8, R9 and R13
2021-05-09 Motor Connector correctly named
2021-05-09 Rename Pins
    Rename ReservePinA10 to pinMotorLeftSense2
2021-05-09 Add I2C Pullup
    Add i2c Pullup to J1 & J3
2021-05-09 Update J30 and J32
2021-05-10 v102
    I have paste my work on the v1.02 hope it's work
2021-05-11 Start ro add Bernard changes from 1.02
2021-05-12 Change I2C Names
2021-05-12 Add Reserve Pin Connectors
2021-05-12 Change Pin Header to JST
    Change Pin Header to JST and sort them on the PCB
2021-05-13 rename folder
2021-05-13 keep initial
2021-05-13 rename
2021-05-13 Add Power Source
    Add Power Source for 5V & 3.3V
2021-05-13 Remove Sonar Resistors
    Remove Sonar Resistors and change Power Source to 3.3V
2021-05-13 Rename I2C Connectors
2021-05-13 Add Pullup to I2C
2021-05-13 Remove RTC Connector
2021-05-13 Add Mounting Hole
2021-05-13 Rename GPS_TX & GPS_RX to RX3 & TX3
2021-05-13 Add ReservePins
2021-05-13 Add Ser0-Ser3
2021-05-13 Rename Button to US1-US3
2021-05-13 Add Footprint for Ser0-Ser3
2021-05-13 Remove 2x4 Motor Pin Connectors
2021-05-13 Add Connector 24V for Motor & Cutter
2021-05-13 Sort Connectors on PCB
2021-05-13 Add Pin Description on PCB
2021-05-13 Add Zener Diode
    3.3 V zener diode to clamp the current sense output voltage to a maximum of ~3.3 V
2021-05-13 Add PCB Pin Description
2021-05-14 Ad Odometrie Connector without Voltage Divider
2021-05-14 Add Voltage Divider to ODO
2021-05-14 Add Voltage Divider
2021-05-15 Sorting Connectors on PCB
2021-05-16 Change direction from i2c Pins
    Change direction from i2c Pins to pass with other pins direction
2021-05-16 Add Motor Connectors
    Add Default Motor Connectors and reorder Ser0-Ser3
2021-05-16 Change PCB Pin Description for Ser0-Ser3
2021-05-16 First Route Test
2021-05-16 Renew Picture
2021-05-16 Small changes in Line Traces
2021-05-16 Add Text and Logos to PCB
2021-05-16 Small Changes
    Change Q2 & Q4 to IRF9540N
    Add Push Button to start the Due
    Change pinChargeEnable to pinChargeRelay
2021-05-16 Rotate PCB_1 Connector to fit with Main PCB
2021-05-16 Only placeholder
2021-05-17 Improve Q2 and Q4
2021-05-17 Drop Pin Summary
2021-05-17 Remove 24V from PCB
2021-05-17 Add 2 new Motor Connectors and Odo
2021-05-17 New Pins added
2021-05-18 Change to JST-XH
2021-05-19 change
    Ardumower is down so can't send last change.
    Here the charging PCB change.
2021-05-19 Rename pinChargeRelay to pinChargeEnable
2021-05-21 Board Route
    Board routed and make Gerber Files
2021-05-21 Add new Image of PCB
2021-05-22 Renew Schematic PDF
2021-06-06 PCB ODO Names Changes
    Change ODO LEFT to Right. Create new Schematic PDF. Create New Gerber Files.
2021-06-06 Delete DUE_PCB_V1.01 directory
    Delete and add Files to 1.00
2021-06-06 Delete charge pcb directory
    Delete it all changes are made
2021-06-06 Add Bernards Changes
2021-06-06 Delete DUE_PCB_V1.02BER directory
    All in default DUE_PCB
2021-06-06 Rename DUE_PCB to v1.01
2021-06-25 Change Q2 and Q4
2021-07-11 Add Schematic PDF and new Picture
2021-07-11 Add Picture of Charging PCB
2021-07-20 Small changes
2021-07-29 Update README.md
    Add Warning to use PowerPCB
